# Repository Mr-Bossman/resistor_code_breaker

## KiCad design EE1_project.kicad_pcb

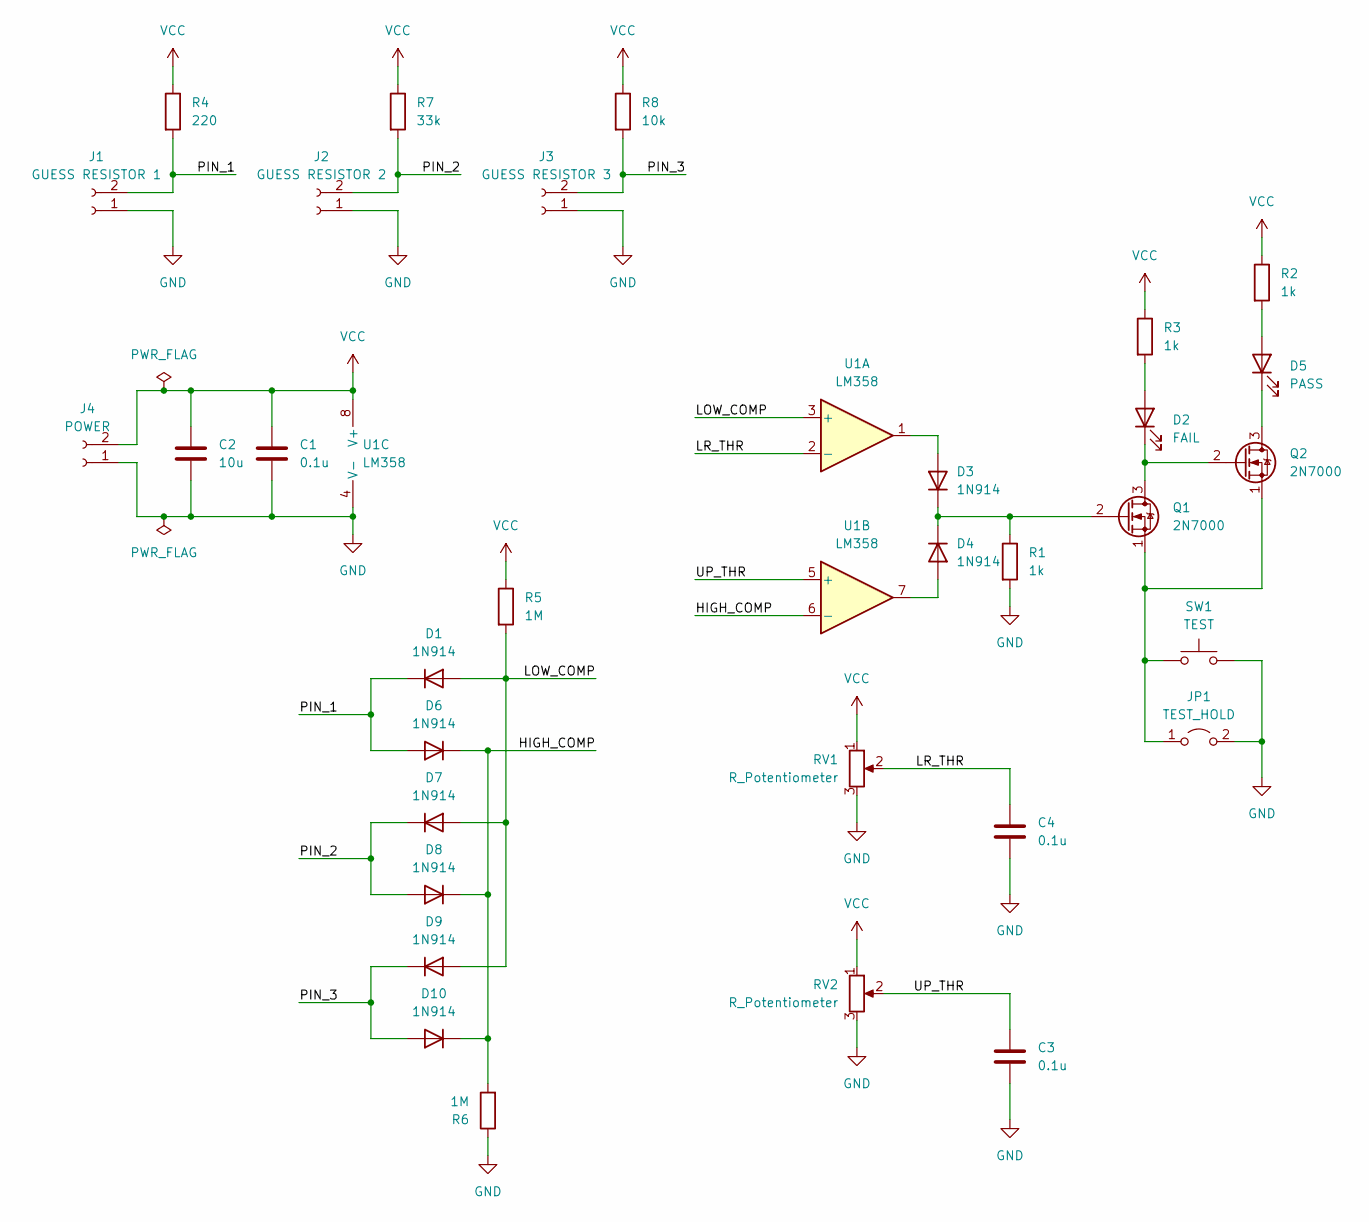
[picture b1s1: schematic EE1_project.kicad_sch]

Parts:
C1, C3, C4: 0.1u; C_0603_1608Metric
C2: 10u; C_1206_3216Metric
D1, D3, D4, D6, D7, D8, D9, D10: 1N914; D_DO-35_SOD27_P7.62mm_Horizontal
D2: FAIL; LED_D5.0mm
D5: PASS; LED_D5.0mm
J1: GUESS RESISTOR 1; PinSocket_2x01_P2.54mm_Vertical
J2: GUESS RESISTOR 2; PinSocket_2x01_P2.54mm_Vertical
J3: GUESS RESISTOR 3; PinSocket_2x01_P2.54mm_Vertical
J4: POWER; PinSocket_2x01_P2.54mm_Vertical
JP1: TEST_HOLD; PinSocket_2x01_P2.54mm_Vertical
Q1, Q2: 2N7000; TO-92_Inline
R1, R2, R3: 1k; C_0603_1608Metric
R4: 220; C_0603_1608Metric
R5, R6: 1M; C_0603_1608Metric
R7: 33k; C_0603_1608Metric
R8: 10k; C_0603_1608Metric
RV1, RV2: R_Potentiometer; Potentiometer_Bourns_3266X_Horizontal
SW1: TEST; SW_PUSH_6mm_H4.3mm
U1: LM358; DIP-8_W7.62mm

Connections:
/HIGH_COMP: D6.1 (K), D8.1 (K), D10.1 (K), R6.2, U1.6 (-)
/LOW_COMP: D1.2 (A), D7.2 (A), D9.2 (A), R5.2, U1.3 (+)
/LR_THR: C4.1, RV1.2, U1.2 (-)
/PIN_1: D1.1 (K), D6.2 (A), J1.2, R4.2
/PIN_2: D7.1 (K), D8.2 (A), J2.2, R7.2
/PIN_3: D9.1 (K), D10.2 (A), J3.2, R8.2
/UP_THR: C3.1, RV2.2, U1.5 (+)
GND: C1.2, C2.2, C3.2, C4.2, J1.1, J2.1, J3.1, J4.1, JP1.2 (B), R1.2, R6.1, RV1.3, RV2.3, SW1.2, U1.4 (V-)
unnamed: D2.2 (A), R3.2
unnamed: D2.1 (K), Q1.3 (D), Q2.2 (G)
unnamed: D3.2 (A), U1.1
unnamed: D3.1 (K), D4.1 (K), Q1.2 (G), R1.1
unnamed: D4.2 (A), U1.7
unnamed: D5.2 (A), R2.2
unnamed: D5.1 (K), Q2.3 (D)
unnamed: JP1.1 (A), Q1.1 (S), Q2.1 (S), SW1.1
VCC: C1.1, C2.1, J4.2, R2.1, R3.1, R4.1, R5.1, R7.1, R8.1, RV1.1, RV2.1, U1.8 (V+)

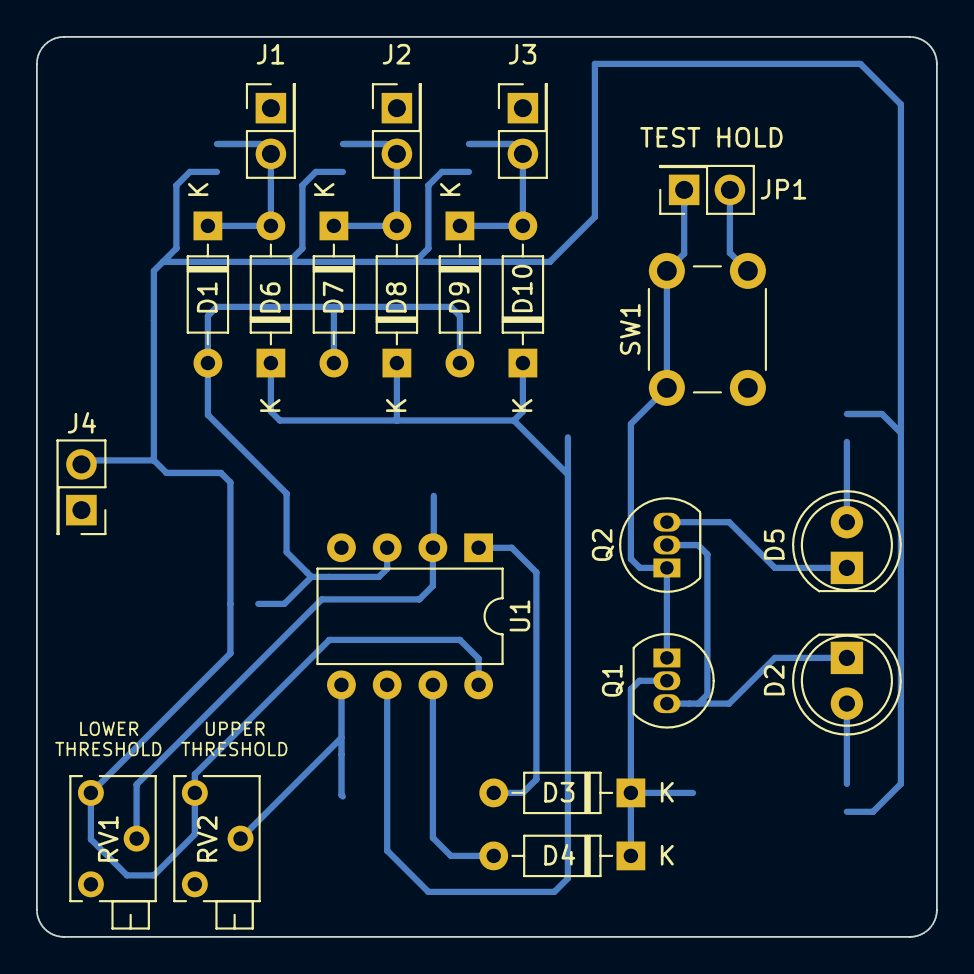
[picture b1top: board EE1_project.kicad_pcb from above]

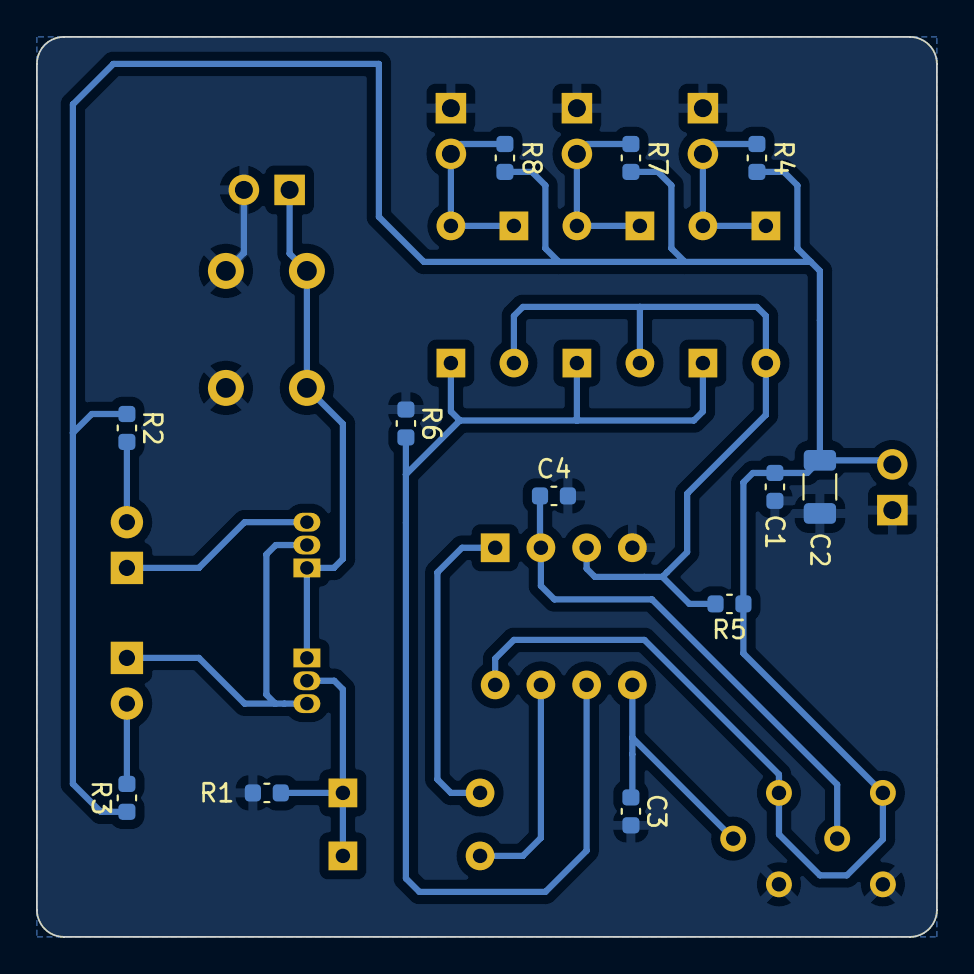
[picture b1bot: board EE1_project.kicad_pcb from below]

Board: 2 copper layers, 50.0 x 50.0 mm, 33 parts (12 on the bottom side), 17 nets.

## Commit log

2024-12-05 init
2024-12-06 flip smd and traces to back
